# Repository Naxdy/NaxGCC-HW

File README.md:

# NaxGCC-HW

The main repository is located at [git.naxdy.org](https://git.naxdy.org/NaxdyOrg/NaxGCC-HW). The GitHub mirror exists solely for the sake of discoverability and redundancy.

> **Please do not submit issues or pull requests on GitHub.**

Find the latest releases here: https://git.naxdy.org/NaxdyOrg/NaxGCC-HW/releases

Full documentation is available at [gcc.naxdy.org](https://gcc.naxdy.org/).

Join the NaxGCC matrix chat at [#naxgcc:naxdy.org](https://matrix.to/#/#naxgcc:naxdy.org) to discuss development or ask for help.

---

Seperate repository for the hardware used in the NaxGCC

The NaxGCC board is licensed under CERN Open Hardware Licence Version 2 - Strongly Reciprocal.
This means that any changes made to the board should be made public.

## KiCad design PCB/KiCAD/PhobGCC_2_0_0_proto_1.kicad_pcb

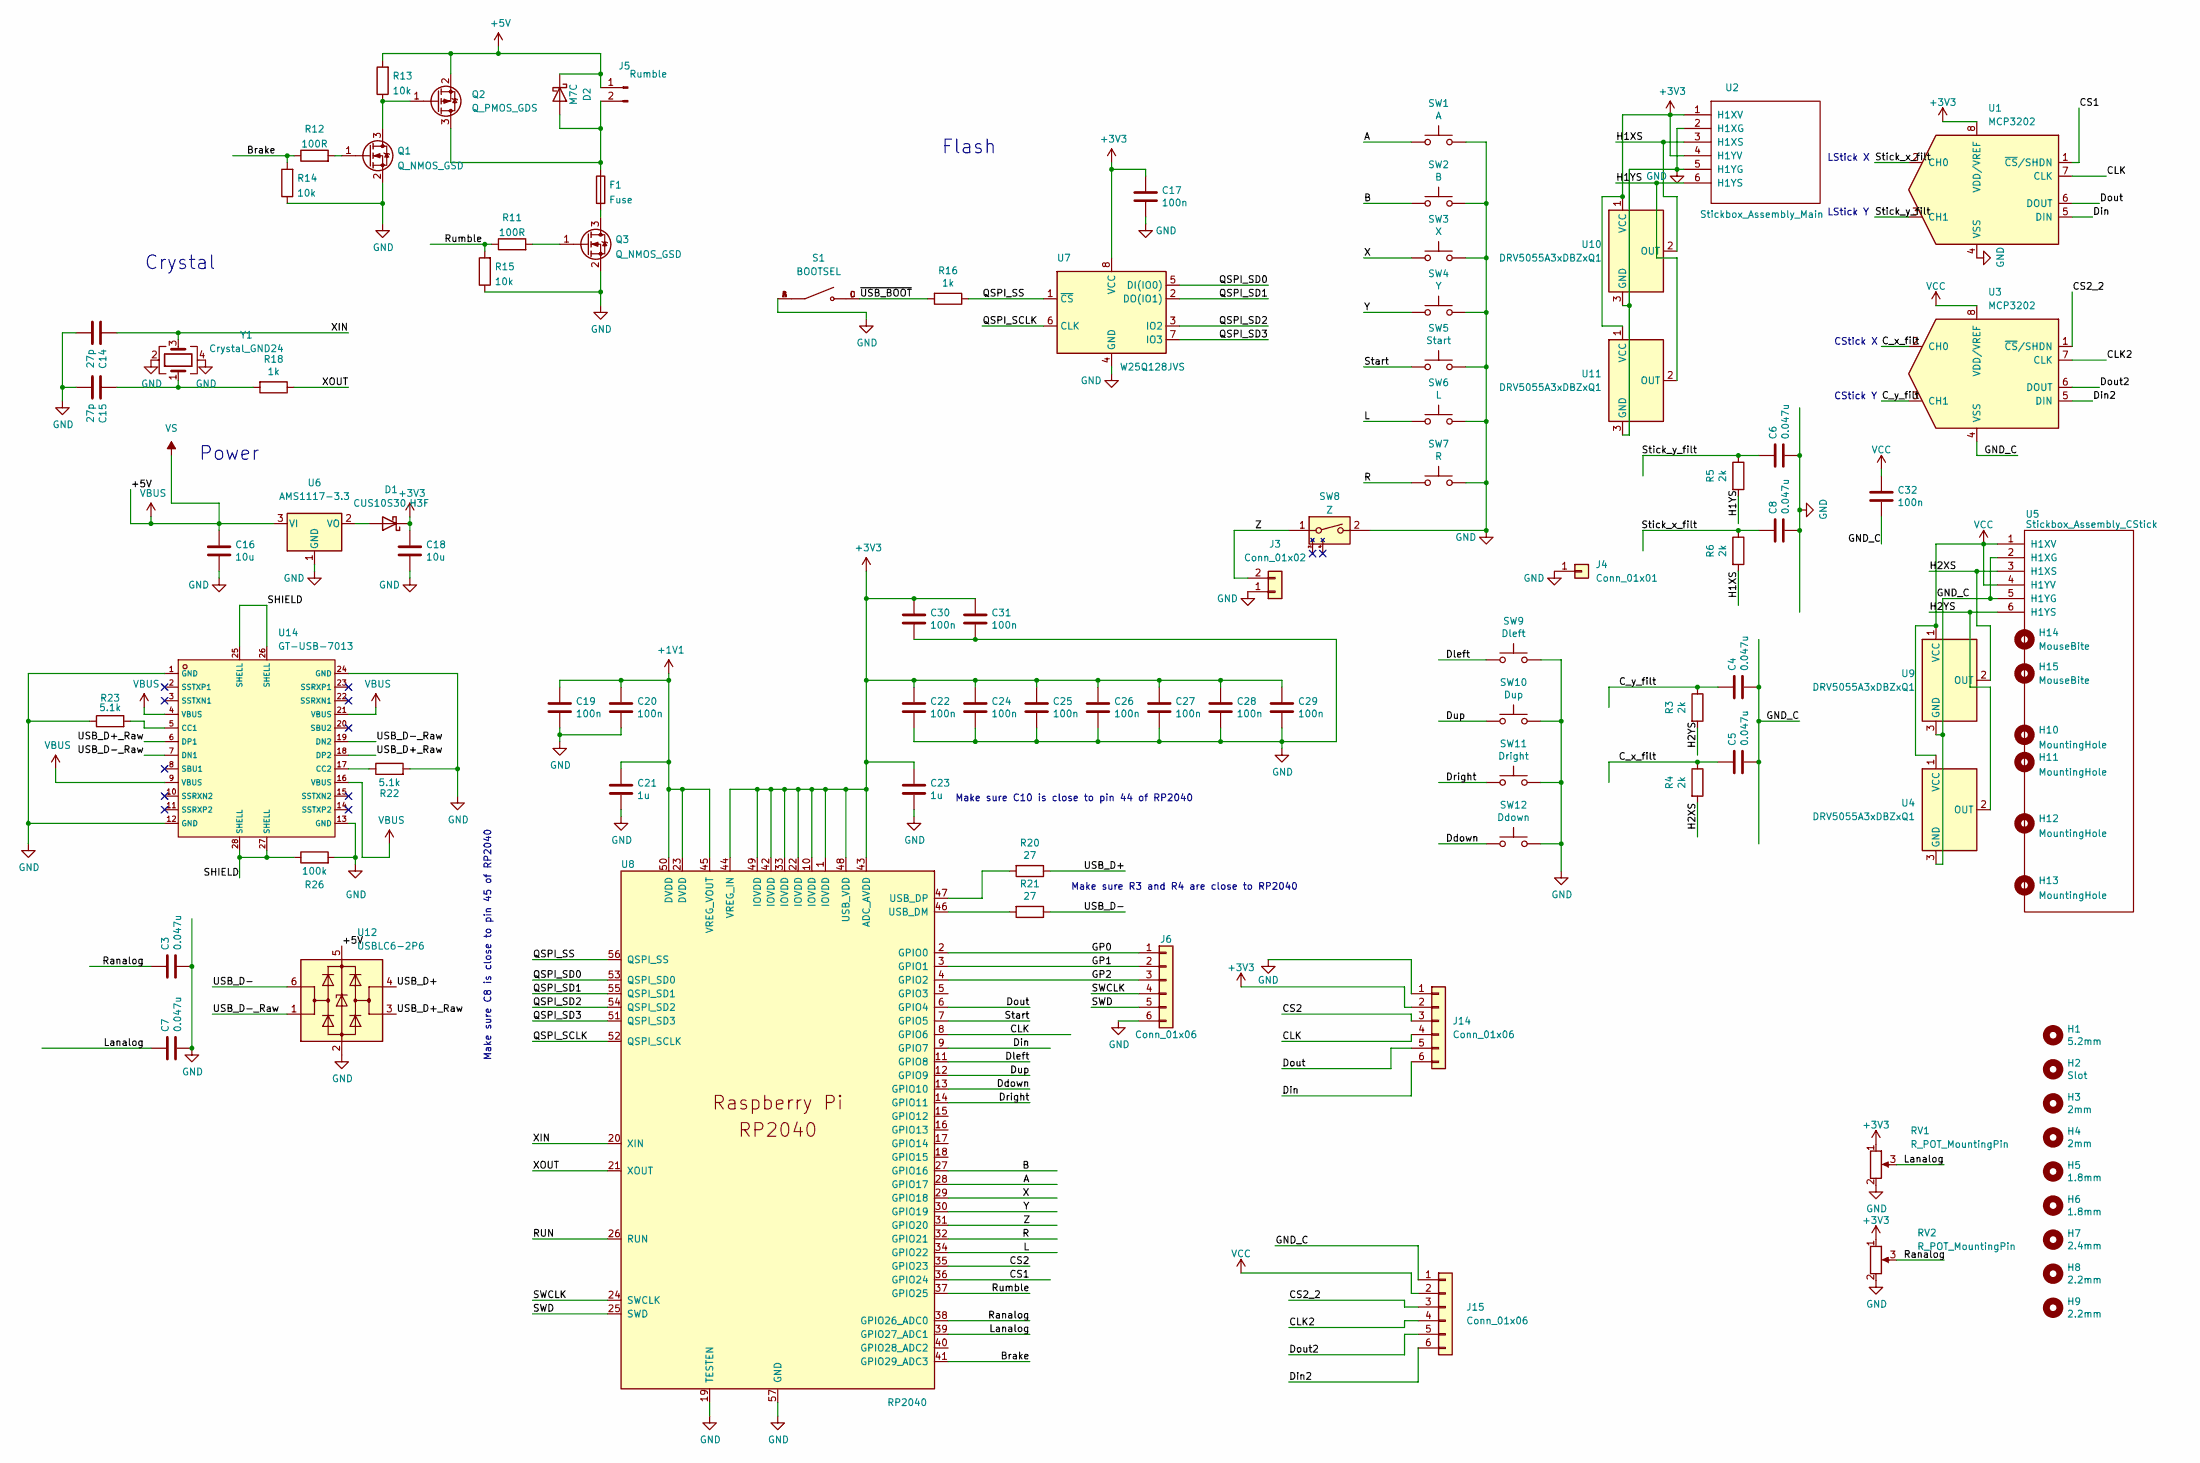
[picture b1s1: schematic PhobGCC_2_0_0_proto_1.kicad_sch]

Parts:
C3, C4, C5, C6, C7, C8: 0.047u; C_0603_HandSoldering; LCSC C1622
C14, C15: 27p; C_0402_1005Metric; LCSC C1557
C16, C18: 10u; C_0805_2012Metric; LCSC C15850
C17, C19, C20, C22, C24, C25, C26, C27, C28, C29, C30, C31, C32: 100n; C_0402_1005Metric; LCSC C1525
C21, C23: 1u; C_0402_1005Metric; LCSC C52923
D1: CUS10S30,H3F; D_SOD-323; LCSC C146335
D2: M7C; D_SOD-123; LCSC C8598
F1: Fuse; Fuse_1206_3216Metric; LCSC C69680
H1: 5.2mm; MountingHole_5.2mm
H2: Slot
H3, H4: 2mm; MountingHole_2.0mm
H5, H6: 1.8mm; MountingHole_1.8mm
H7: 2.4mm; MountingHole_2.4mm
H8, H9: 2.2mm; MountingHole_2.2mm
H10: MountingHole; MountingHole_1.8mm
H11: MountingHole; MountingHole_5.2mm
H12, H13: MountingHole; MountingHole_2.0mm
H14: MouseBite; breakaway-mousebites-double-v2-small
H15: MouseBite; breakaway-mousebites-double-v2-large
J3: Conn_01x02; PinHeader_1x02_P2.00mm_Horizontal
J4: Conn_01x01; PinHeader_1x01_P2.54mm_Vertical
J5: Rumble; rumble_pins
J6, J14, J15: Conn_01x06; PinSocket_1x06_P2.00mm_Vertical
Q1, Q3: Q_NMOS_GSD; SOT-23; LCSC C20917
Q2: Q_PMOS_GDS; SOT-23; LCSC C15127
R3, R4, R5, R6: 2k; R_0603_1608Metric_Pad0.98x0.95mm_HandSolder; LCSC C22975
R11, R12: 100R; R_0603_1608Metric_Pad0.98x0.95mm_HandSolder; LCSC C22775
R13, R14, R15: 10k; R_0603_1608Metric_Pad0.98x0.95mm_HandSolder; LCSC C25804
R16, R18: 1k; C_0402_1005Metric; LCSC C11702
R20, R21: 27; C_0402_1005Metric; LCSC C25100
R22, R23: 5.1k; R_0402_1005Metric; LCSC C25905
R26: 100k; R_0603_1608Metric_Pad0.98x0.95mm_HandSolder; LCSC C25803
RV1, RV2: R_POT_MountingPin; GCC_Slider
S1: BOOTSEL; SW_TS-1187A-B-A-B; PARTREV A0; LCSC C318884
SW1: A; ABXY_Contact_Omron_Switch_Circley
SW2: B; ABXY_Contact_Omron_Switch_Circley
SW3: X; ABXY_Contact_Omron_Switch_Circley
SW4: Y; ABXY_Contact_Omron_Switch_Circley
SW5: Start; Start_Contact
SW6: L; Pin_Header_Straight_1x02_Pitch2.54mm
SW7: R; Pin_Header_Straight_1x02_Pitch2.54mm
SW8: Z; Z_Switch_Edge_Omron
SW9: Dleft; Dpad_Contact_TL3315NF_2_ZigZag
SW10: Dup; Dpad_Contact_TL3315NF_2_ZigZag
SW11: Dright; Dpad_Contact_TL3315NF_2_ZigZag
SW12: Ddown; Dpad_Contact_TL3315NF_2_ZigZag
U1, U3: MCP3202; SOIC-8_3.9x4.9mm_P1.27mm; LCSC C56997
U2: Stickbox_Assembly_Main; GCC_Stickbox_Hall_Only
U4, U9, U10, U11: DRV5055A3xDBZxQ1; SOT-23; LCSC C266128
U5: Stickbox_Assembly_CStick; GCC_Stickbox_Hall_Only
U6: AMS1117-3.3; SOT-223-3_TabPin2; LCSC C6186
U7: W25Q128JVS; SOIC-8_5.23x5.23mm_P1.27mm; LCSC C97521
U8: RP2040; RP2040-QFN-56; LCSC C2040
U12: USBLC6-2P6; SOT-666; LCSC C2827693
U14: GT-USB-7013; USB-C-SMD_GT-USB-7013; LCSC C2762992
Y1: Crystal_GND24; Crystal_SMD_3225-4Pin_3.2x2.5mm; LCSC C403945

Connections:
+1V1: C19.1, C20.1, C21.1, U8.23 (DVDD), U8.45 (VREG_VOUT), U8.50 (DVDD)
+3V3: C17.1, C18.1, C22.1, C23.1, C24.1, C25.1, C26.1, C27.1, C28.1, C29.1, C30.1, C31.1, D1.1 (K), J14.2, RV1.1 (V+), RV2.1 (V+), U1.8 (VDD/VREF), U2.1 (H1XV), U2.4 (H1YV), U7.8 (VCC), U8.1 (IOVDD), U8.10 (IOVDD), U8.22 (IOVDD), U8.33 (IOVDD), U8.42 (IOVDD), U8.43 (ADC_AVDD), U8.44 (VREG_IN), U8.48 (USB_VDD), U8.49 (IOVDD), U10.1 (VCC), U11.1 (VCC)
+5V: C16.1, D2.1 (K), J5.1, Q2.2 (S), R13.2, U6.3 (VI), U12.5 (VBUS), U14.4 (VBUS), U14.9 (VBUS), U14.16 (VBUS), U14.21 (VBUS)
/A: SW1.1, U8.28 (GPIO17)
/B: SW2.1, U8.27 (GPIO16)
/Brake: R12.1, R14.2, U8.41 (GPIO29_ADC3)
/CLK: J14.4, U1.7 (CLK), U8.8 (GPIO6)
/CLK2: J15.4, U3.7 (CLK)
/CS1: U1.1 (~CS/SHDN), U8.36 (GPIO24)
/CS2: J14.3, U8.35 (GPIO23)
/CS2_2: J15.3, U3.1 (~CS/SHDN)
/C_x_filt: C5.1, R4.1, U3.2 (CH0)
/C_y_filt: C4.1, R3.1, U3.3 (CH1)
/Ddown: SW12.1, U8.13 (GPIO10)
/Din: J14.6, U1.5 (DIN), U8.9 (GPIO7)
/Din2: J15.6, U3.5 (DIN)
/Dleft: SW9.1, U8.11 (GPIO8)
/Dout: J14.5, U1.6 (DOUT), U8.6 (GPIO4)
/Dout2: J15.5, U3.6 (DOUT)
/Dright: SW11.1, U8.14 (GPIO11)
/Dup: SW10.1, U8.12 (GPIO9)
/GND_C: C4.2, C5.2, C32.2, J15.1, U3.4 (VSS), U4.3 (GND), U5.2 (H1XG), U5.5 (H1YG), U9.3 (GND)
/GP0: J6.1, U8.2 (GPIO0)
/GP1: J6.2, U8.3 (GPIO1)
/GP2: J6.3, U8.4 (GPIO2)
/H1XS: R6.2, U2.3 (H1XS), U10.2 (OUT)
/H1YS: R5.2, U2.6 (H1YS), U11.2 (OUT)
/H2XS: R4.2, U5.3 (H1XS), U9.2 (OUT)
/H2YS: R3.2, U4.2 (OUT), U5.6 (H1YS)
/L: SW6.1, U8.34 (GPIO22)
/Lanalog: C7.1, RV1.3 (Signal), U8.39 (GPIO27_ADC1)
/QSPI_SCLK: U7.6 (CLK), U8.52 (QSPI_SCLK)
/QSPI_SD0: U7.5 (DI(IO0)), U8.53 (QSPI_SD0)
/QSPI_SD1: U7.2 (DO(IO1)), U8.55 (QSPI_SD1)
/QSPI_SD2: U7.3 (IO2), U8.54 (QSPI_SD2)
/QSPI_SD3: U7.7 (IO3), U8.51 (QSPI_SD3)
/QSPI_SS: R16.1, U7.1 (~CS), U8.56 (QSPI_SS)
/R: SW7.1, U8.32 (GPIO21)
/RUN: U8.26 (RUN)
/Ranalog: C3.1, RV2.3 (Signal), U8.38 (GPIO26_ADC0)
/Rumble: R11.1, R15.2, U8.37 (GPIO25)
/SHIELD: R26.1, U14.25 (SHELL), U14.26 (SHELL), U14.27 (SHELL), U14.28 (SHELL)
/SWCLK: J6.4, U8.24 (SWCLK)
/SWD: J6.5, U8.25 (SWD)
/Start: SW5.1, U8.7 (GPIO5)
/Stick_x_filt: C8.1, R6.1, U1.2 (CH0)
/Stick_y_filt: C6.1, R5.1, U1.3 (CH1)
/USB_D+: R20.1, U12.4 (I/O2)
/USB_D+_Raw: U12.3 (I/O2), U14.6 (DP1), U14.18 (DP2)
/USB_D-: R21.1, U12.6 (I/O1)
/USB_D-_Raw: U12.1 (I/O1), U14.7 (DN1), U14.19 (DN2)
/X: SW3.1, U8.29 (GPIO18)
/XIN: C14.1, U8.20 (XIN), Y1.3
/XOUT: R18.1, U8.21 (XOUT)
/Y: SW4.1, U8.30 (GPIO19)
/Z: J3.2, SW8.1, U8.31 (GPIO20)
/~USB_BOOT: R16.2, S1.C, S1.D
GND: C3.2, C6.2, C7.2, C8.2, C14.2, C15.2, C16.2, C17.2, C18.2, C19.2, C20.2, C21.2, C22.2, C23.2, C24.2, C25.2, C26.2, C27.2, C28.2, C29.2, C30.2, C31.2, J3.1, J4.1, J6.6, J14.1, Q1.2 (S), Q3.2 (S), R14.1, R15.1, R22.2, R23.1, R26.2, RV1.2 (GND), RV2.2 (GND), S1.A, S1.B, SW1.2, SW2.2, SW3.2, SW4.2, SW5.2, SW6.2, SW7.2, SW8.2, SW9.2, SW10.2, SW11.2, SW12.2, U1.4 (VSS), U2.2 (H1XG), U2.5 (H1YG), U6.1 (GND), U7.4 (GND), U8.19 (TESTEN), U8.57 (GND), U10.3 (GND), U11.3 (GND), U12.2 (GND), U14.1 (GND), U14.12 (GND), U14.13 (GND), U14.24 (GND), Y1.2, Y1.4
unnamed: C15.1, R18.2, Y1.1
unnamed: D1.2 (A), U6.2 (VO)
unnamed: D2.2 (A), F1.1, J5.2, Q2.3 (D)
unnamed: Q1.3 (D), Q2.1 (G), R13.1
unnamed: Q1.1 (G), R12.2
unnamed: F1.2, Q3.3 (D)
unnamed: Q3.1 (G), R11.2
unnamed: R21.2, U8.46 (USB_DM)
unnamed: R20.2, U8.47 (USB_DP)
unnamed: R23.2, U14.5 (CC1)
unnamed: R22.1, U14.17 (CC2)
VCC: C32.1, J15.2, U3.8 (VDD/VREF), U4.1 (VCC), U5.1 (H1XV), U5.4 (H1YV), U9.1 (VCC)

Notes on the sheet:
Power
LStick Y
Make sure C10 is close to pin 44 of RP2040
CStick Y
Make sure R3 and R4 are close to RP2040
Make sure C8 is close to pin 45 of RP2040
Flash
Crystal
CStick X
LStick X

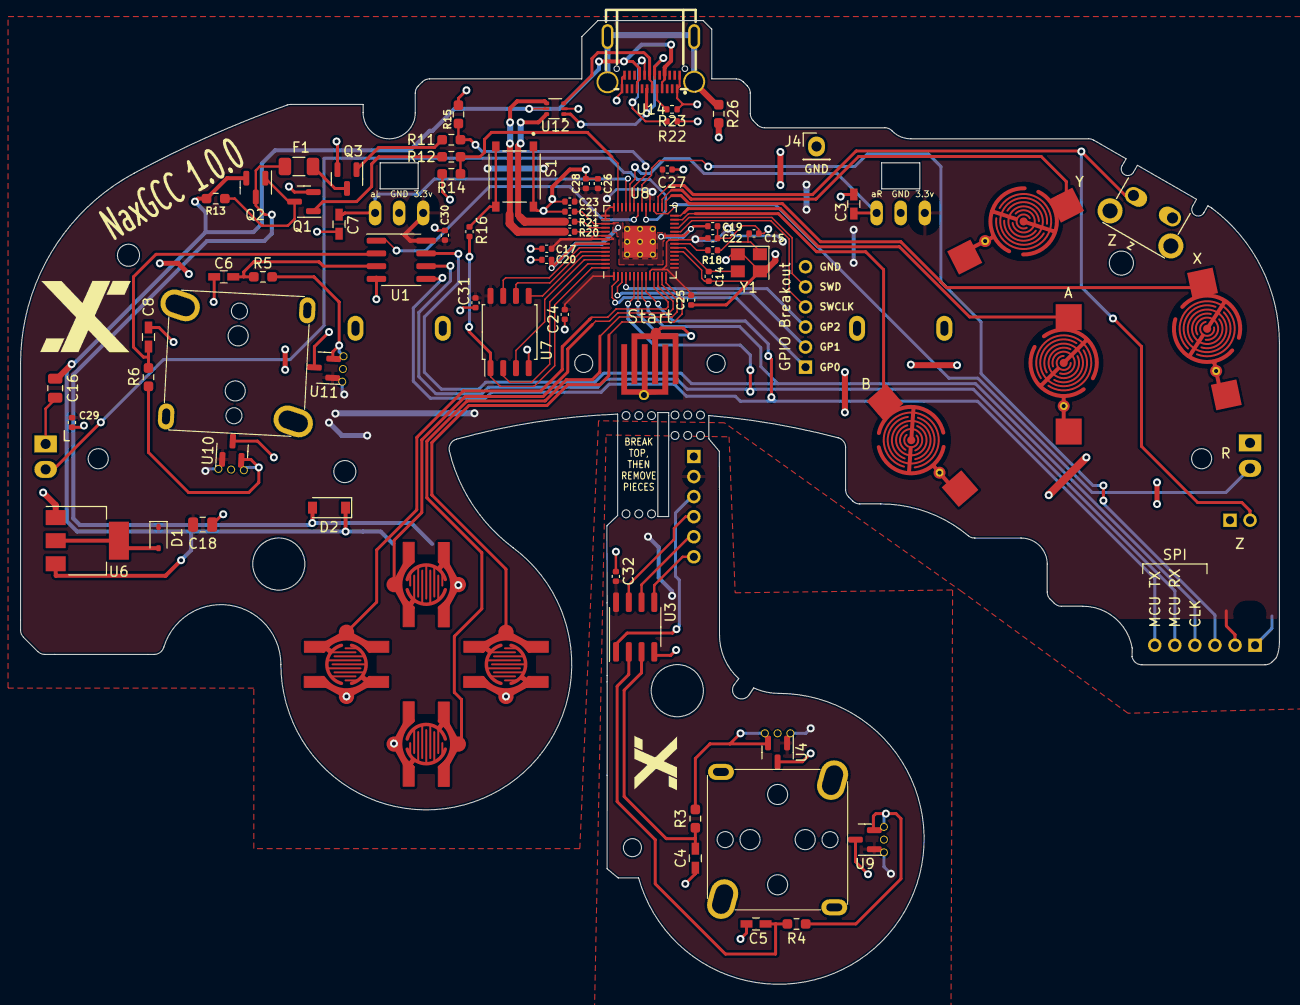
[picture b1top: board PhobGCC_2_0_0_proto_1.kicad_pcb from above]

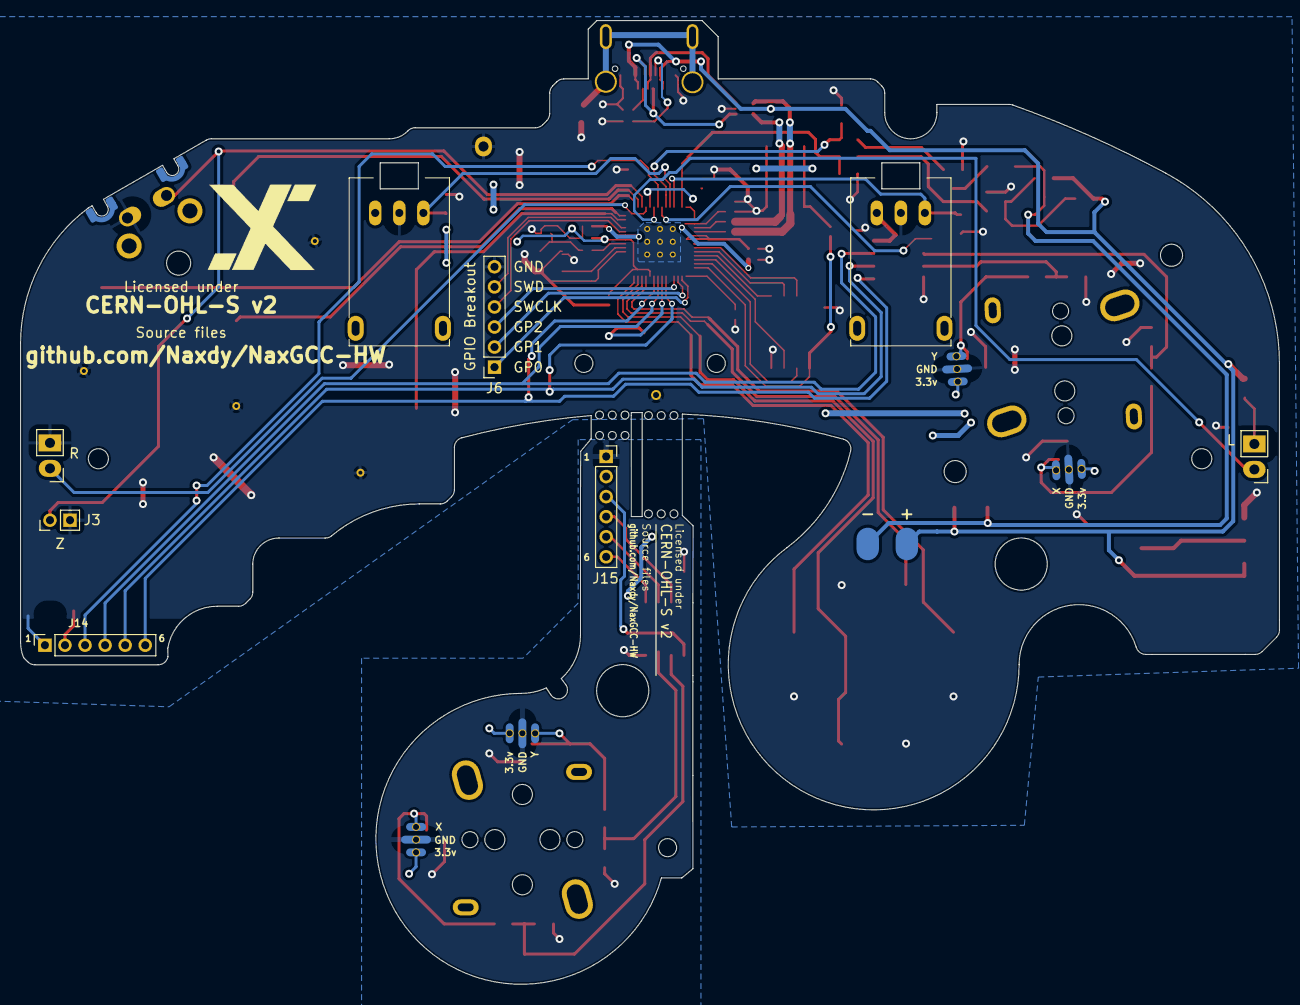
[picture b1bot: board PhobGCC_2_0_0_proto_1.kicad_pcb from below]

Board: 2 copper layers, 125.5 x 96.1 mm, 97 parts (9 on the bottom side), 69 nets.

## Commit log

2024-04-05 NaxGCC Changes:
    - update to KiCad 8
    - replace micro USB & GCC connector with USB C
    - add some JLCPCB symbols, footprints & models
2024-04-09 chore(readme): add repo info
2024-04-11 chore(readme): add matrix link
2024-04-15 chore(ci): add github action for PR's

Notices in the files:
PCB/KiCAD/PhobGCC_2_0_0_proto_1.kicad_pcb:
CERN-OHL-S v2
